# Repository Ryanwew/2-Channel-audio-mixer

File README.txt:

This project is used to create a 2 chanel audio mixer, each input into the controller is mixed with the other, the ratio of the output is controlled by the 2 Potentiometers. Fully compatible with left/right channels

For assembly, solder components onto PCB, insert PCB into enclosure, drill holes into enclosure faceplates, use nuts to secure and cover with printed knobs.

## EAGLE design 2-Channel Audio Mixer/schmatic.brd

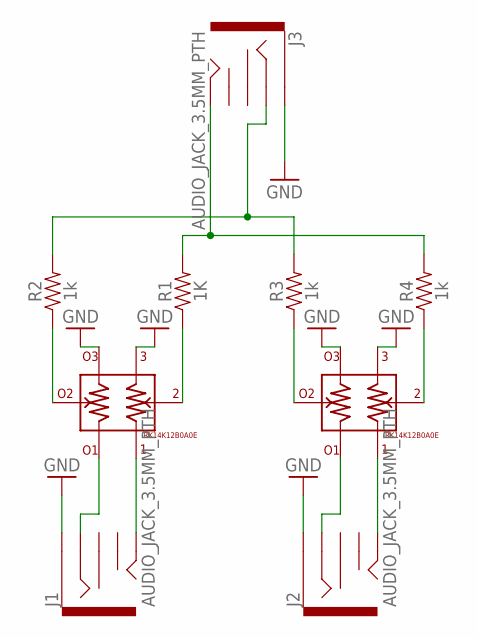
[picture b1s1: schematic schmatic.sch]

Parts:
J1, J2, J3: AUDIO_JACK_3.5MM_PTH; AUDIO-JACK
POT01, POT02: RK14K12B0A0E
R1: 1K; AXIAL-0.3
R2, R3, R4: 1k; AXIAL-0.3

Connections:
GND: J1.SLEEVE, J2.SLEEVE, J3.SLEEVE, POT01.3, POT01.O3, POT02.3, POT02.O3
unnamed: POT02.O2, R2.P$1 (1)
unnamed: POT02.2, R1.P$1 (1)
unnamed: POT01.O2, R3.P$1 (1)
unnamed: POT01.2, R4.P$1 (1)
unnamed: J2.RING, POT01.O1
unnamed: J2.TIP, POT01.1
unnamed: J3.RING, R2.P$2 (2), R3.P$2 (2)
unnamed: J3.TIP, R1.P$2 (2), R4.P$2 (2)
unnamed: J1.TIP, POT02.1
unnamed: J1.RING, POT02.O1

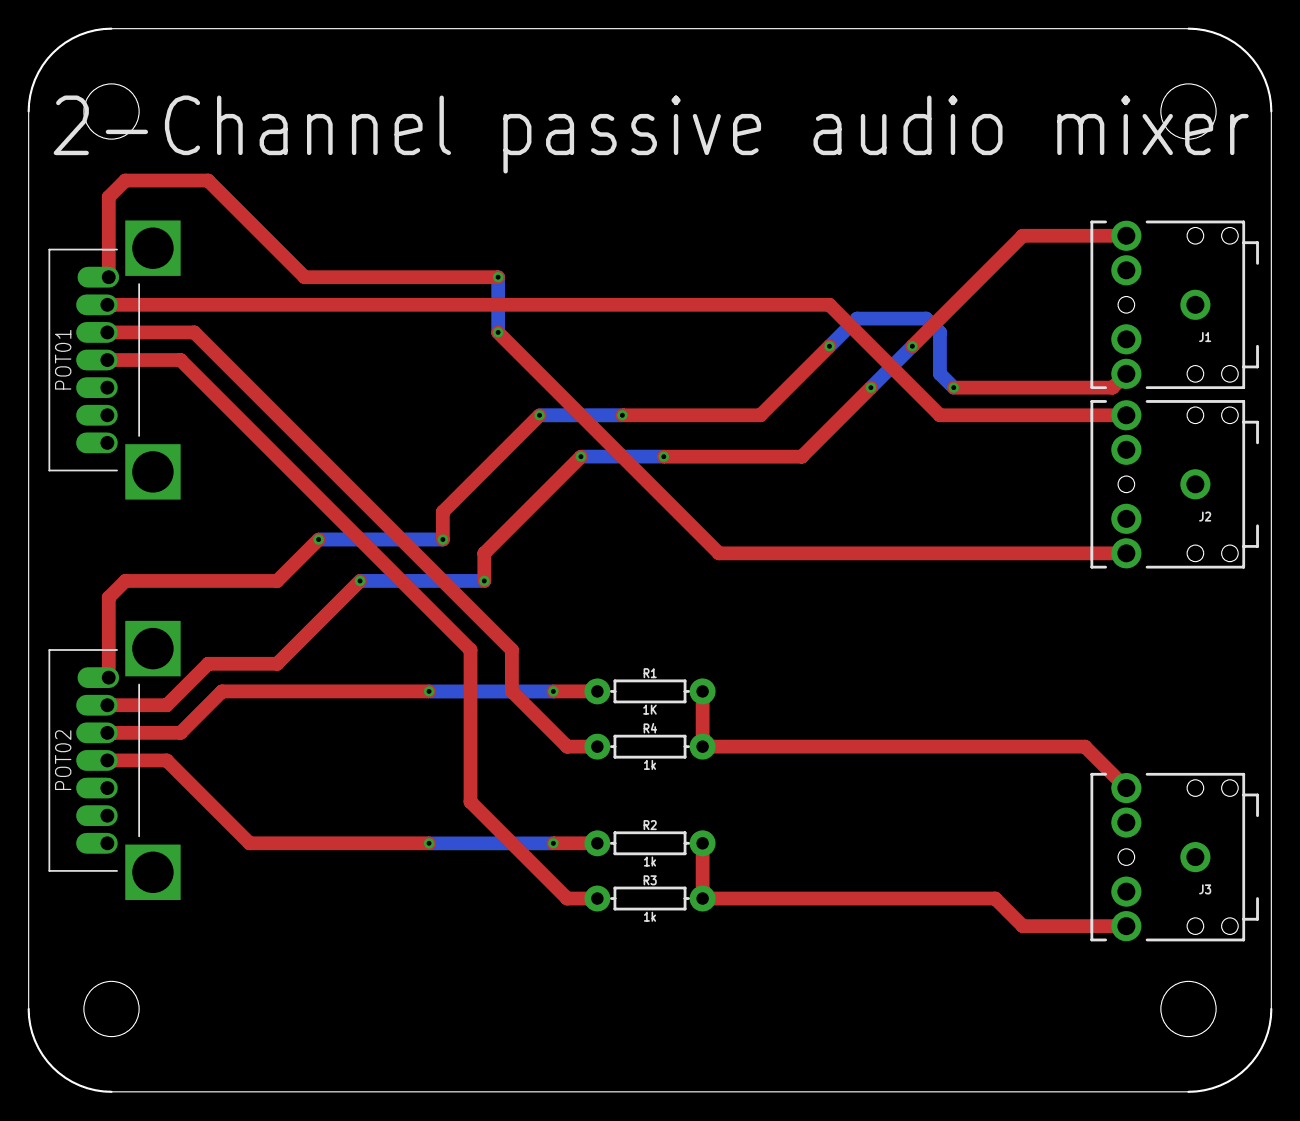
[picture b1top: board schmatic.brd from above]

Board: 2 copper layers, 90.0 x 77.0 mm, 9 parts (0 on the bottom side), 11 nets.

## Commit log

2020-12-21 Project Creation
2020-12-21 Fixed BOM

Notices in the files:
parts and their libraries:
SparkFun-Resistors: Licensing: Creative Commons ShareAlike 4.0 International - https://creativecommons.org/licenses/by-sa/4.0
